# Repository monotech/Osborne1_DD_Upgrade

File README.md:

# Osborne1_DD_Upgrade
Exact replica of the Double Density floppy upgrade board for the Osborne 1

Every part except the PCB can be bought from proper distributors such as Mouser, Digikey, Farnell/element14, LCSC, etc. Avoid chips from Aliexpress/eBay.

Licensed under CC BY-SA 4.0 (https://creativecommons.org/licenses/by-sa/4.0/)

You can share, change, sell, but you must give credit and provide your adaptations under the same license.

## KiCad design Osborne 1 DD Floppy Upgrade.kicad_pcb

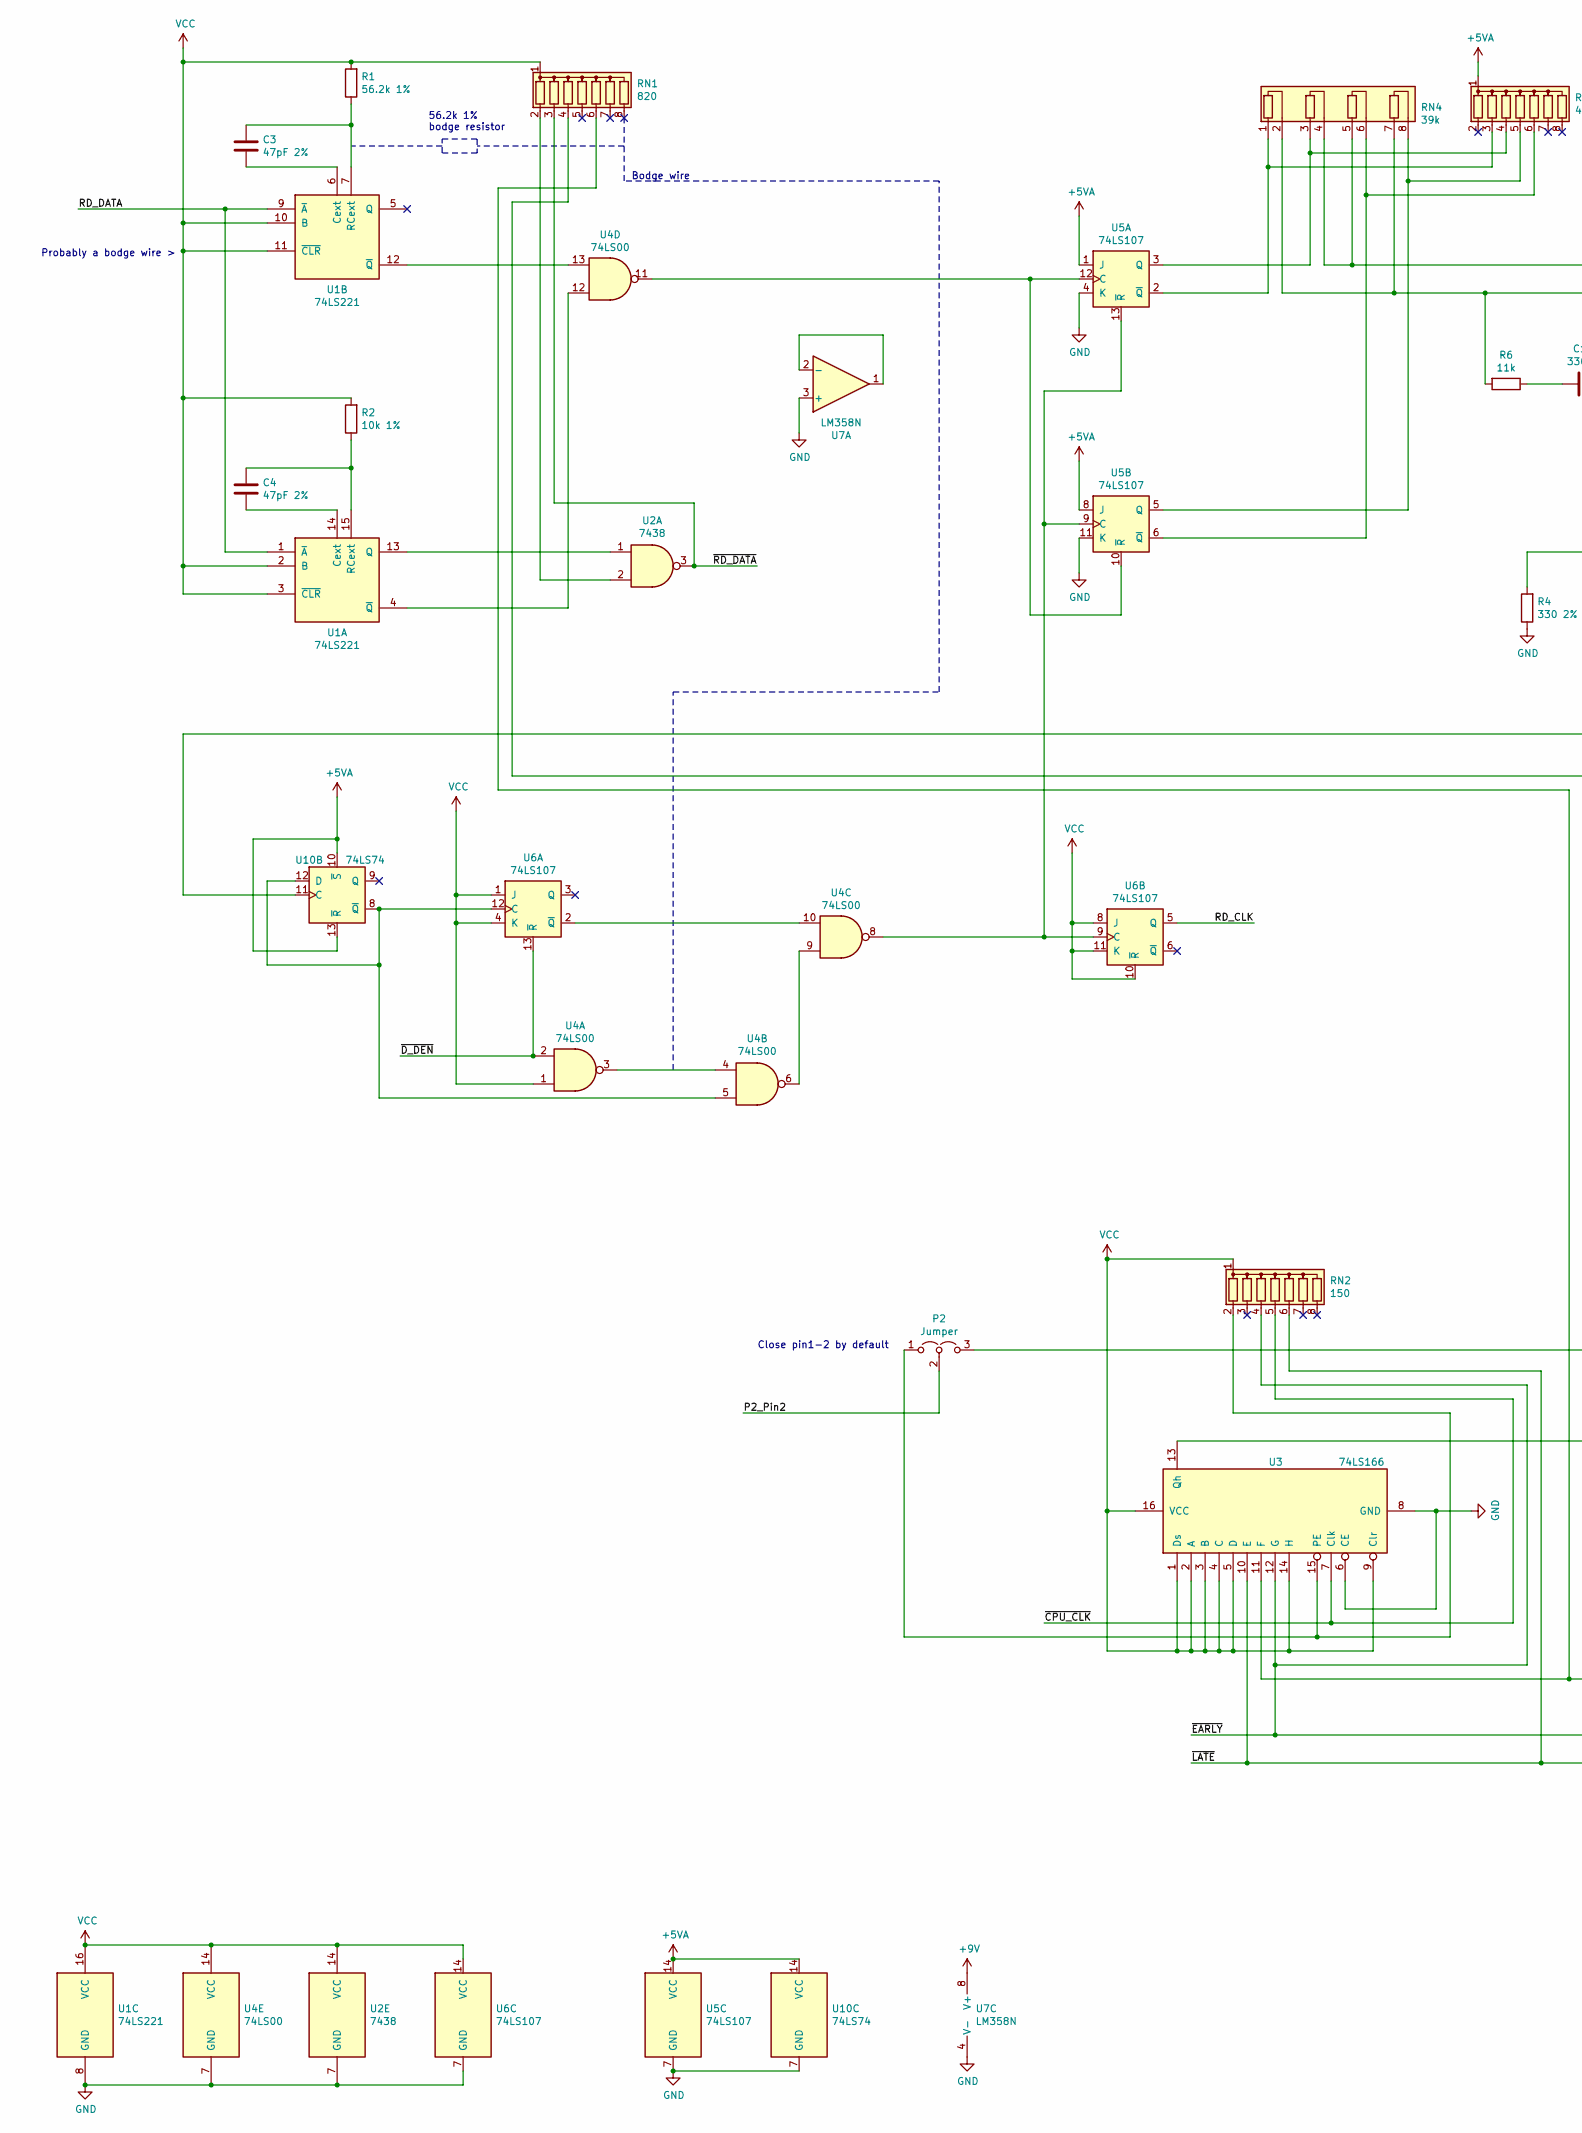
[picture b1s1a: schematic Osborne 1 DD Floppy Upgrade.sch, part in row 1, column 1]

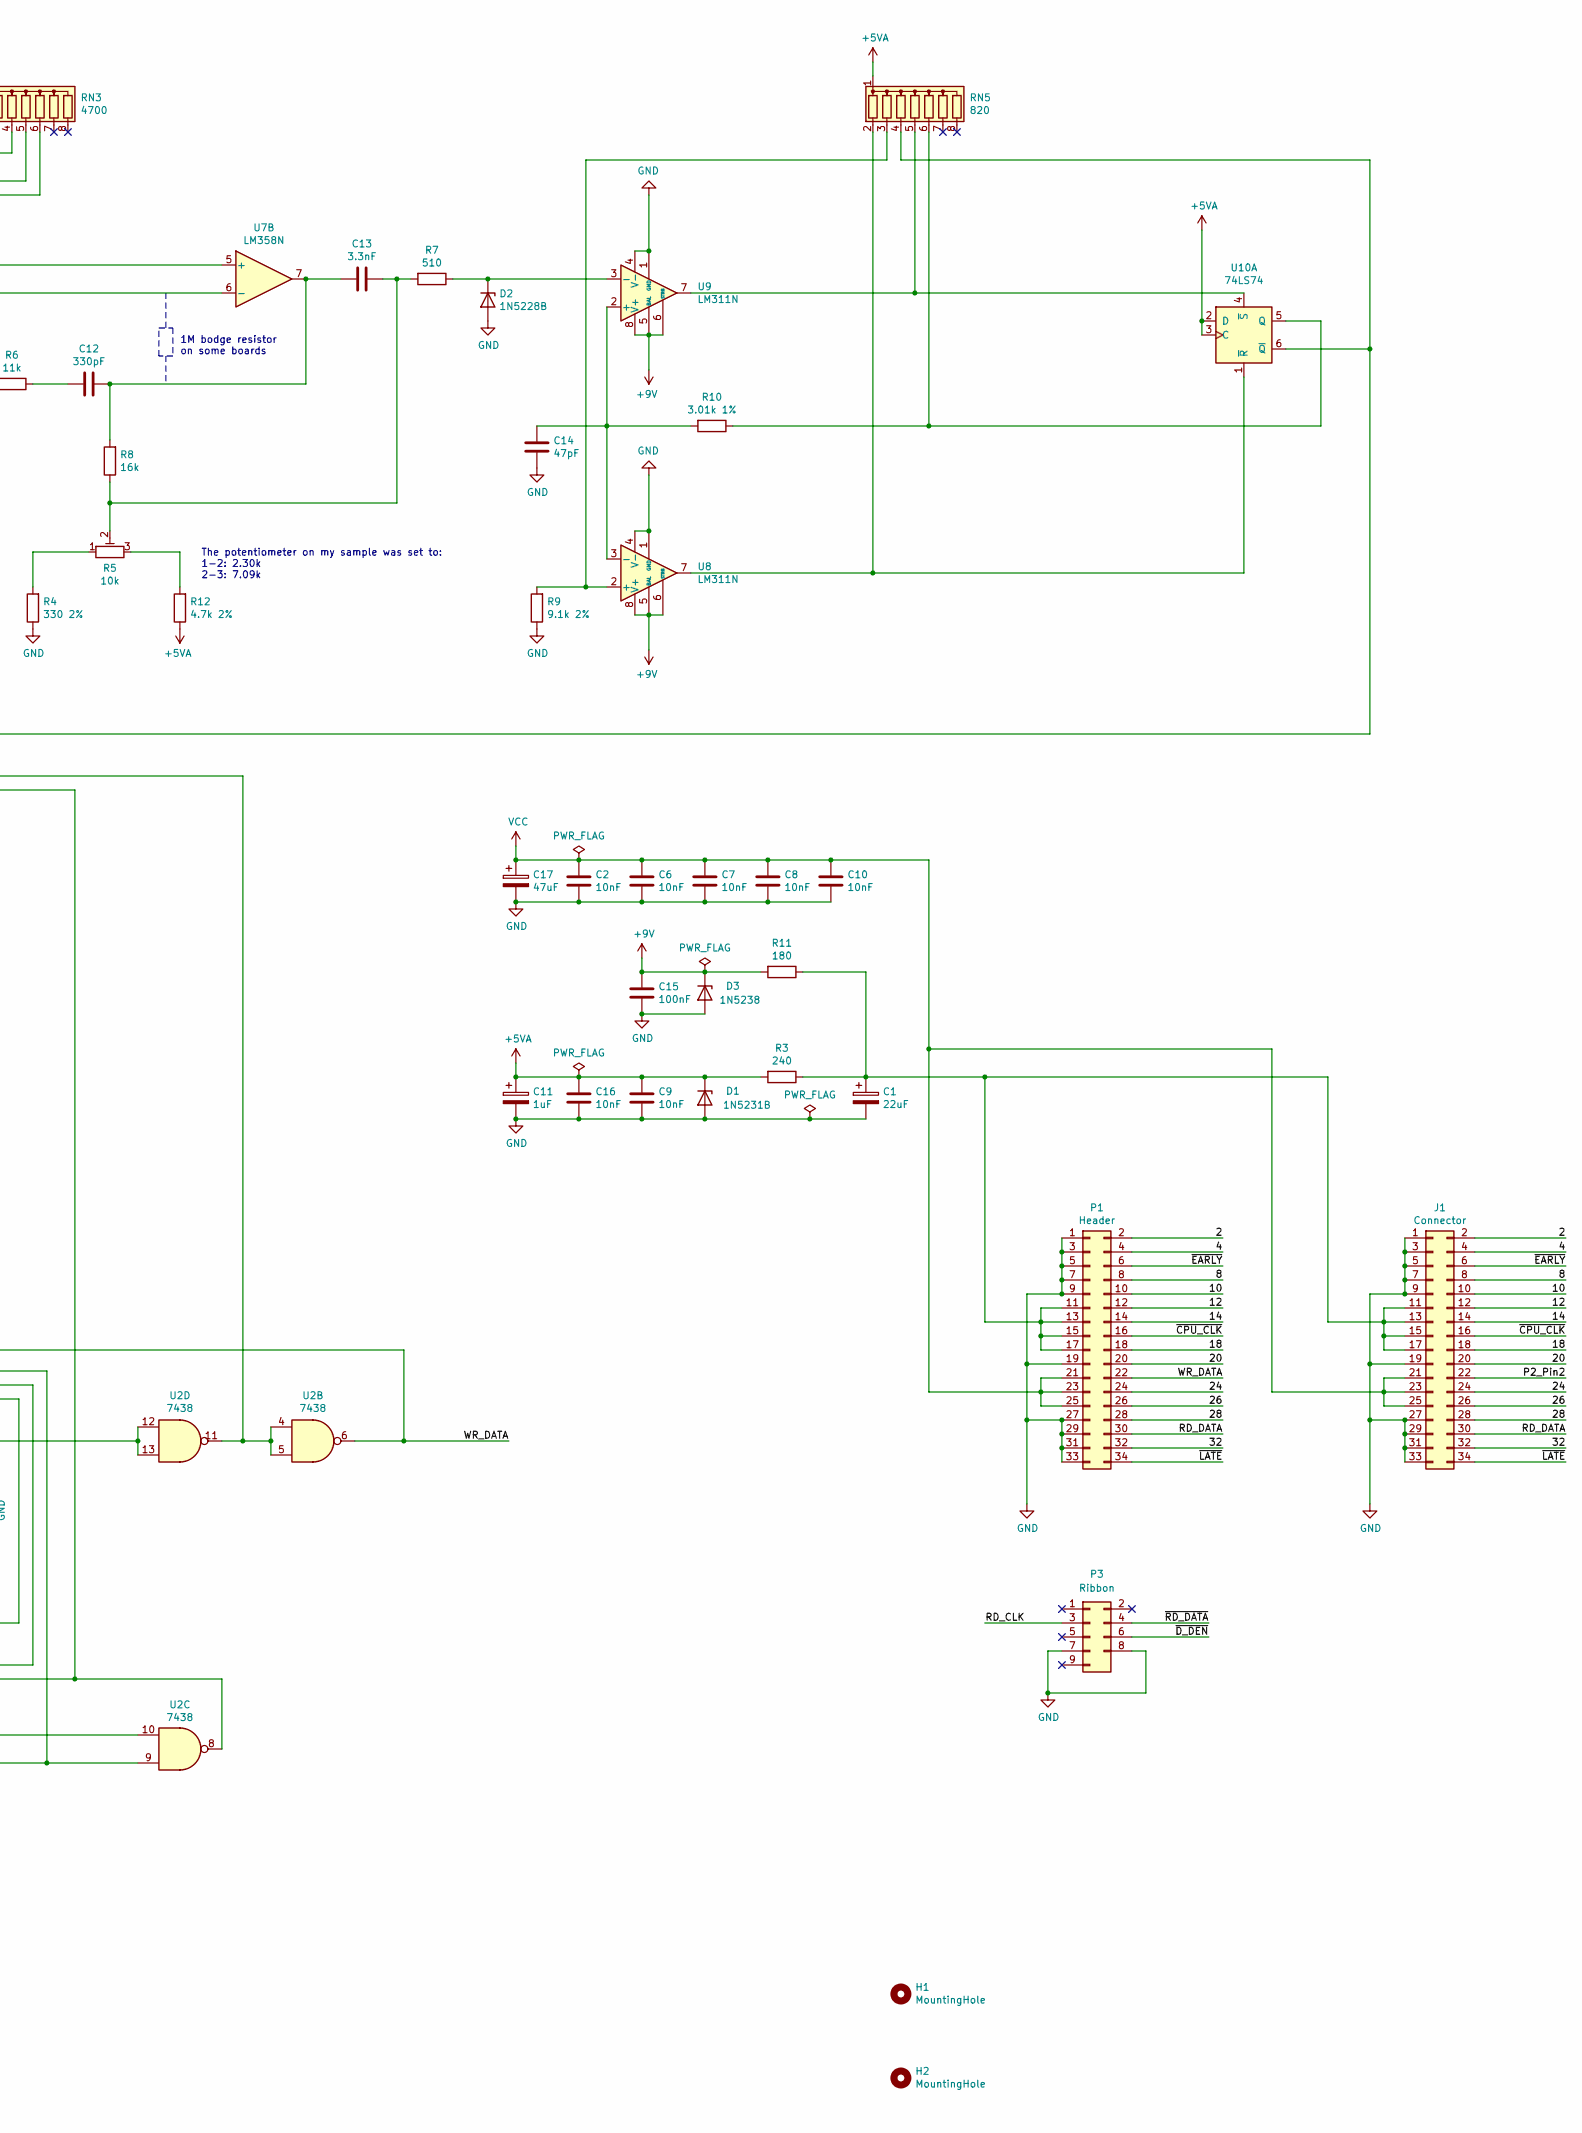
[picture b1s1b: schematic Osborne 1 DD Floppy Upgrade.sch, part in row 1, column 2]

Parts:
C1: 22uF; CP_Radial_D5.0mm_P2.50mm
C2, C6, C7, C8, C9, C10, C16: 10nF; R_Axial_DIN0207_L6.3mm_D2.5mm_P10.16mm_Horizontal
C3: 47pF 2%; C_Rect_L11.0mm_W3.5mm_P10.00mm_MKT
C4: 47pF 2%; C_Rect_L4.0mm_W2.5mm_P2.50mm
C11: 1uF; CP_Radial_Tantal_D4.5mm_P2.50mm
C12: 330pF; R_Axial_DIN0207_L6.3mm_D2.5mm_P10.16mm_Horizontal
C13: 3.3nF; R_Axial_DIN0207_L6.3mm_D2.5mm_P10.16mm_Horizontal
C14: 47pF; C_Disc_D3.0mm_W2.0mm_P2.50mm
C15: 100nF; R_Axial_DIN0207_L6.3mm_D2.5mm_P10.16mm_Horizontal
C17: 47uF; CP_Radial_D5.0mm_P2.50mm
D1: 1N5231B; D_DO-35_SOD27_P10.16mm_Horizontal
D2: 1N5228B; D_DO-35_SOD27_P10.16mm_Horizontal
D3: 1N5238; D_DO-35_SOD27_P10.16mm_Horizontal
H1, H2: MountingHole; MountingHole_4mm
J1: Connector; PinHeader_2x17_P2.54mm_Vertical
P1: Header; PinHeader_2x17_P2.54mm_Vertical
P2: Jumper; PinHeader_1x03_P2.54mm_Vertical
P3: Ribbon; PinHeader_2x05_P2.54mm_Vertical
R1: 56.2k 1%; R_Axial_DIN0207_L6.3mm_D2.5mm_P10.16mm_Horizontal
R2: 10k 1%; R_Axial_DIN0207_L6.3mm_D2.5mm_P10.16mm_Horizontal
R3: 240; R_Axial_DIN0207_L6.3mm_D2.5mm_P10.16mm_Horizontal
R4: 330 2%; R_Axial_DIN0207_L6.3mm_D2.5mm_P10.16mm_Horizontal
R5: 10k; Potentiometer_Vishay_T73YP_Vertical
R6: 11k; R_Axial_DIN0207_L6.3mm_D2.5mm_P10.16mm_Horizontal
R7: 510; R_Axial_DIN0207_L6.3mm_D2.5mm_P10.16mm_Horizontal
R8: 16k; R_Axial_DIN0207_L6.3mm_D2.5mm_P10.16mm_Horizontal
R9: 9.1k 2%; R_Axial_DIN0207_L6.3mm_D2.5mm_P10.16mm_Horizontal
R10: 3.01k 1%; R_Axial_DIN0207_L6.3mm_D2.5mm_P10.16mm_Horizontal
R11: 180; R_Axial_DIN0207_L6.3mm_D2.5mm_P10.16mm_Horizontal
R12: 4.7k 2%; R_Axial_DIN0207_L6.3mm_D2.5mm_P10.16mm_Horizontal
RN1, RN5: 820; R_Array_SIP8
RN2: 150; R_Array_SIP8
RN3: 4700; R_Array_SIP8
RN4: 39k; R_Array_SIP8
U1: 74LS221; DIP-16_W7.62mm
U2: 7438; DIP-14_W7.62mm
U3: 74LS166; DIP-16_W7.62mm
U4: 74LS00; DIP-14_W7.62mm
U5, U6: 74LS107; DIP-14_W7.62mm
U7: LM358N; DIP-8_W7.62mm
U8, U9: LM311N; DIP-8_W7.62mm
U10: 74LS74; DIP-14_W7.62mm

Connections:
+5VA: C9.1, C11.1, C16.1, D1.1 (K), R3.2, R12.1, RN3.1 (common), RN5.1 (common), U5.1 (J), U5.8 (J), U5.14 (VCC), U10.2 (D), U10.3 (C), U10.10 (~S), U10.13 (~R), U10.14 (VCC)
+9V: C15.1, D3.1 (K), R11.2, U7.8 (V+), U8.5 (BAL), U8.6 (STRB), U8.8 (V+), U9.5 (BAL), U9.6 (STRB), U9.8 (V+)
/2: J1.2, P1.2
/4: J1.4, P1.4
/8: J1.8, P1.8
/10: J1.10, P1.10
/12: J1.12, P1.12
/14: J1.14, P1.14
/18: J1.18, P1.18
/20: J1.20, P1.20
/24: J1.24, P1.24
/26: J1.26, P1.26
/28: J1.28, P1.28
/32: J1.32, P1.32
/P2_Pin2: J1.22, P2.2 (C)
/RD_CLK: P3.3, U6.5 (Q)
/RD_DATA: J1.30, P1.30, U1.1 (~A), U1.9 (~A)
/WR_DATA: P1.22, P2.3 (B), U2.6
/~CPU_CLK: J1.16, P1.16, RN2.5 (R4), U3.7 (Clk)
/~D_DEN: P3.6, U4.2, U6.13 (~R)
/~EARLY: J1.6, P1.6, RN2.4 (R3), U2.10, U3.12 (G)
/~LATE: J1.34, P1.34, RN2.6 (R5), U2.9, U3.10 (E)
/~RD_DATA: P3.4, RN1.3 (R2), U2.3
GND: C1.2, C2.2, C6.2, C7.2, C8.2, C9.2, C10.2, C11.2, C14.2, C15.2, C16.2, C17.2, D1.2 (A), D2.2 (A), D3.2 (A), J1.1, J1.3, J1.5, J1.7, J1.9, J1.19, J1.27, J1.29, J1.31, J1.33, P1.1, P1.3, P1.5, P1.7, P1.9, P1.19, P1.27, P1.29, P1.31, P1.33, P3.7, P3.8, R4.1, R9.1, U1.8 (GND), U2.7 (GND), U3.6 (CE), U3.8 (GND), U4.7 (GND), U5.4 (K), U5.7 (GND), U5.11 (K), U6.7 (GND), U7.3 (+), U7.4 (V-), U8.1 (GND), U8.4 (V-), U9.1 (GND), U9.4 (V-), U10.7 (GND)
unnamed: C1.1, J1.11, J1.13, J1.15, J1.17, P1.11, P1.13, P1.15, P1.17, R3.1, R11.1
unnamed: C3.1, R1.1, U1.7 (RCext)
unnamed: C3.2, U1.6 (Cext)
unnamed: C4.1, R2.1, U1.15 (RCext)
unnamed: C4.2, U1.14 (Cext)
unnamed: C12.1, C13.2, R8.2, U7.7
unnamed: C12.2, R6.1
unnamed: C13.1, R5.2, R7.2, R8.1
unnamed: C14.1, R10.2, U8.3 (-), U9.2 (+)
unnamed: D2.1 (K), R7.1, U9.3 (-)
unnamed: P2.1 (A), RN2.2 (R1), U3.15 (PE)
unnamed: R4.2, R5.1
unnamed: R6.2, RN4.2 (R1.2), RN4.7 (R4.1), U7.6 (-)
unnamed: R9.2, RN5.3 (R2), U8.2 (+)
unnamed: R10.1, RN5.6 (R5), U10.5 (Q)
unnamed: R5.3, R12.2
unnamed: RN1.2 (R1), U2.2
unnamed: RN1.4 (R3), U2.4, U2.5, U2.11
unnamed: RN1.6 (R5), U2.8, U3.11 (F)
unnamed: RN3.3 (R2), RN4.1 (R1.1), U5.2 (~Q)
unnamed: RN3.4 (R3), RN4.3 (R2.1), U5.3 (Q)
unnamed: RN3.5 (R4), RN4.8 (R4.2), U5.5 (Q)
unnamed: RN3.6 (R5), RN4.6 (R3.2), U5.6 (~Q)
unnamed: RN4.4 (R2.2), RN4.5 (R3.1), U7.5 (+)
unnamed: RN5.2 (R1), U8.7, U10.1 (~R)
unnamed: RN5.4 (R3), U10.6 (~Q), U10.11 (C)
unnamed: RN5.5 (R4), U9.7, U10.4 (~S)
unnamed: U1.4 (~Q), U4.12
unnamed: U1.12 (~Q), U4.13
unnamed: U1.13 (Q), U2.1
unnamed: U2.12, U2.13, U3.13 (Qh)
unnamed: U4.3, U4.4
unnamed: U4.6, U4.9
unnamed: U4.8, U5.9 (C), U5.13 (~R), U6.9 (C)
unnamed: U4.10, U6.2 (~Q)
unnamed: U4.11, U5.10 (~R), U5.12 (C)
unnamed: U7.1, U7.2 (-)
unnamed: U4.5, U6.12 (C), U10.8 (~Q), U10.12 (D)
VCC: C2.1, C6.1, C7.1, C8.1, C10.1, C17.1, J1.21, J1.23, J1.25, P1.21, P1.23, P1.25, R1.2, R2.2, RN1.1 (common), RN2.1 (common), U1.2 (B), U1.3 (~CLR), U1.10 (B), U1.11 (~CLR), U1.16 (VCC), U2.14 (VCC), U3.1 (Ds), U3.2 (A), U3.3 (B), U3.4 (C), U3.5 (D), U3.9 (Clr), U3.14 (H), U3.16 (VCC), U4.1, U4.14 (VCC), U6.1 (J), U6.4 (K), U6.8 (J), U6.10 (~R), U6.11 (K), U6.14 (VCC)

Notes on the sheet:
56.2k 1% bodge resistor
Close pin1-2 by default
Bodge wire
1M bodge resistor on some boards
Probably a bodge wire >
The potentiometer on my sample was set to: 1-2: 2.30k 2-3: 7.09k

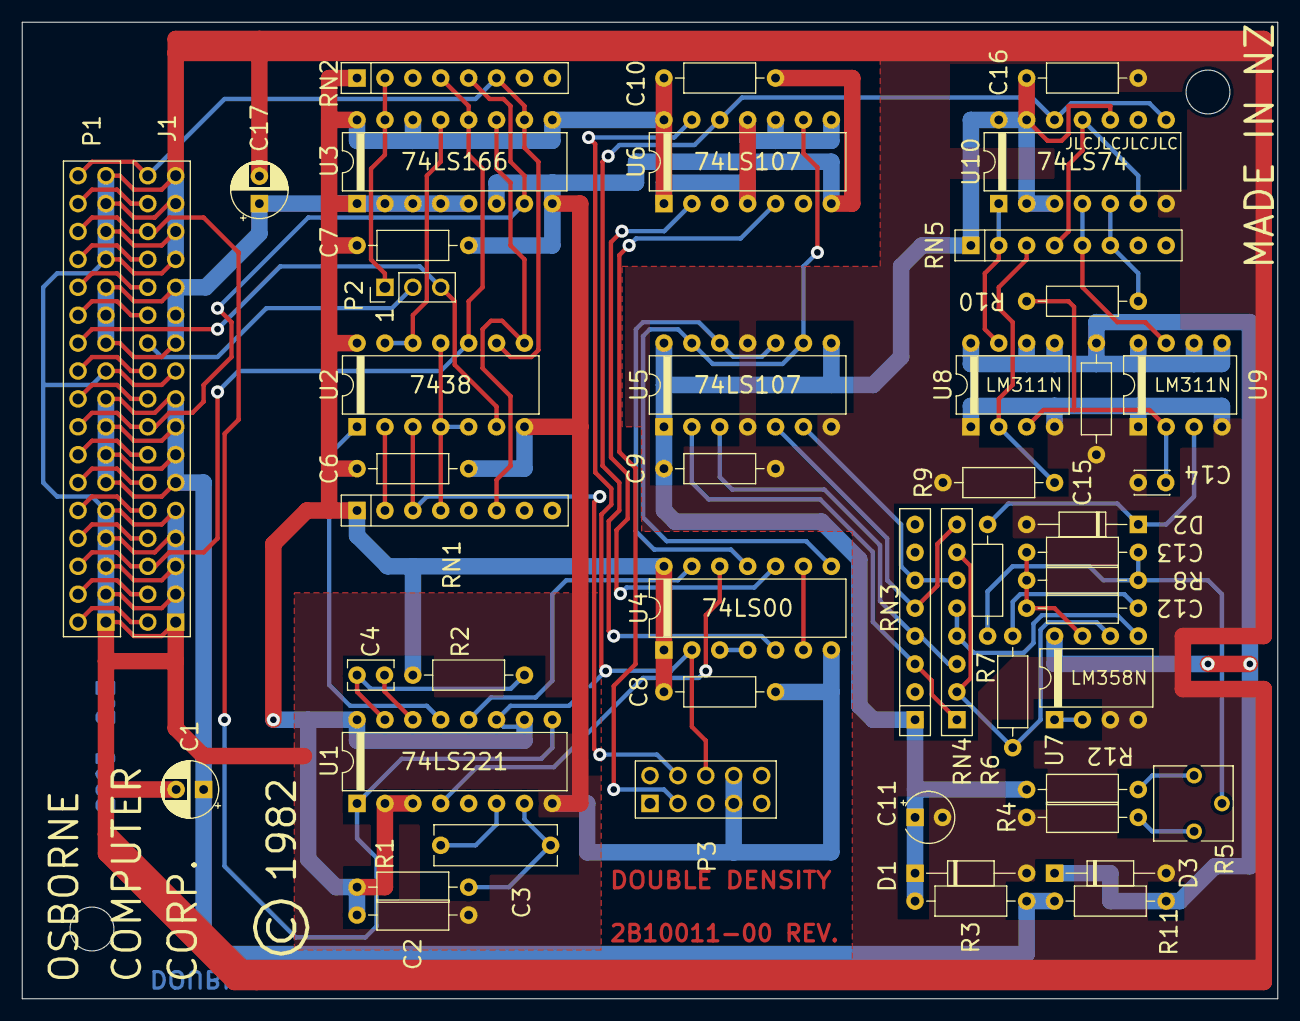
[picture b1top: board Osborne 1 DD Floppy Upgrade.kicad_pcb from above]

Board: 2 copper layers, 114.3 x 88.9 mm, 52 parts (0 on the bottom side), 63 nets.
